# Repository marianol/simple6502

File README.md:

# simple6502

My own take on a simple 6502 single board computer, inspired on Garth Wilson's excellent 6502 Primer, Daryl Rictor, Ben Eater, and my own beautiful C=64 and all the classic 8-bit computers of the late 70s early 80s.

This project exists because of scope creep on my YAsixfive02 project, which is in its 10000 iteration. Which I don't think will ever end.

## Organization

The project is organized as follows:

- /hardware
    - /simple6502 The SBC computer motherboard a.k.a The Project
    - /IO_Card A 6522 IO card with 2 VIAs
    - /protoCard A protoboard card for the simple6502 to build your projects
    - /6502motherboard An untested but complete card connector backplane motherboard. I decided to abandon this in favor of the SBC, i may pick it up later
    - /schematics PDF schematics and renders
    - /gallery images of the completed PCBs
    - /3dmodels Kicad 3D models
- /firmware
    - BIOS and ROM for the simple6502, check the ReadMe
- /docs
    - docs will be here for now only datasheets 

## Design

The goal is to build a simple 6502 SBC with RAM, ROM, IO decoding and a serial interface. An expansion  bus will carry all the address, data and supporting lines to allow adding IO and other hardware expansions. The PCB will be kept at 100x100mm to reduce cost.

For the serial interface I settled on the Motorola 68B50 ACIA, just because I had one lying around. This forced using a 1.8432MHz clock that drives both the CPU and the ACIA. I added a header for an FTDI card to convert the TTL serial to USB. The ACIA is connected to the IO_8 line locating it at 0x7F70 in the memory map.
The jumper J2 next to the header allows you to run the board with the USB 5v rail from the FTDI. IMPORTANT!! This overrides the power switch SW2 and there is no protection built into the board so you should not connect this jumper at the same time as the 5V barrel J7 or the AUX Power header J8.
The bus Slot connectors have pin 27 tied to IO_1 and IO_2 respectively allowing to design expansion cards that can be mapped into memory based on where they are plugged. You still have access to IO_3 to IO_7 in case you want to use those. The Expansion Port J1 is intended to be used with a 40 pin ribbon for ease of development of prototype boards.

I made the PCBs for Revision 1.6 on PCBWay. 

## Status

**Revision 1.6:**

- PCB built and tested.
- BIOS 0.0.1 working on Rev 1.6. Minimal BIOS routines to control the ACIA

## Memory Map

Momory Decocing is done using gates for RAM, ROM and IO. IO_CS line is sent to a 3-8 decoder to get 8 individual IO select lines.
IO line  $\overline{IO\textunderscore08}$ is used for the onboard ACIA for serial communication.
IO lines  $\overline{IO\textunderscore01}$ and $\overline{IO\textunderscore02}$ are sent to pin 27 of Slot 1 and 2 respectively. This allows cards that use this pin to get mapped to the memory based on the Slot they are inserted.

I should have mapped some IO on Zero Page for ease of programming and fast IO, but that is left for another revision, since is too convoluted with gates and better suited for a PAL/GAL. 

### Address Space

- 0x0000 - 0x7EFF : RAM 32K - 256 bytes (31.75k)
- 0x7F00 - 0x7F0F : IO_1 > SLOT 1
- 0x7F10 - 0x7F1F : IO_2 > SLOT 2
- 0x7F20 - 0x7F2F : IO_3
- 0x7F30 - 0x7F3F : IO_4
- 0x7F40 - 0x7F4F : IO_5
- 0x7F50 - 0x7F5F : IO_6
- 0x7F60 - 0x7F6F : IO_7
- 0x7F70 - 0x7F7F : IO_8 > ACIA
- 0x7F80 - 0x7FFF : Not Decoded
- 0x8000 - 0xFFFF : ROM (32K)

## Card Connector Design

The card connector is based on the EDAC 395 series. I decided on the 395-50-520-201 which I had from a previous Apple ][ repair.
Exposed in the connector are:

- Address lines A0..A15
- Data lines D0..D7
- Clock $\phi$ 2
- $\overline{IO{\textunderscore}CS}$, $\overline{RAM{\textunderscore}CS}$ , and $\overline{ROM{\textunderscore}CS}$ chip select lines
- $\overline{RD}$ and $\overline{WR}$ 
- $\overline{RESET}$
- Pin 27 is the slot IO select line. For Slot 1 is $\overline{IO\textunderscore01}$ mapping it to 0x7F00, and for Slot 2 is $\overline{IO\textunderscore02}$ mapping it to 0x7F10.
- IO chip select lines $\overline{IO\textunderscore03}$ .. $\overline{IO\textunderscore07}$.
- $\overline{IRQ}$ and $\overline{NMI}$
- VCC and GND, this are set so if you insert a card backwards you will not short them.
- Pins 21, 24, 33, and 34 are only connected between the 2 slots and have no connection to the mainboard 

## Licence

Licenced under CERN Open Hardware licence CERN-OHL-S v2, see CERN-OHL-S-v2.txt

(c) 2023-2024 Mariano Luna. All rights reserved

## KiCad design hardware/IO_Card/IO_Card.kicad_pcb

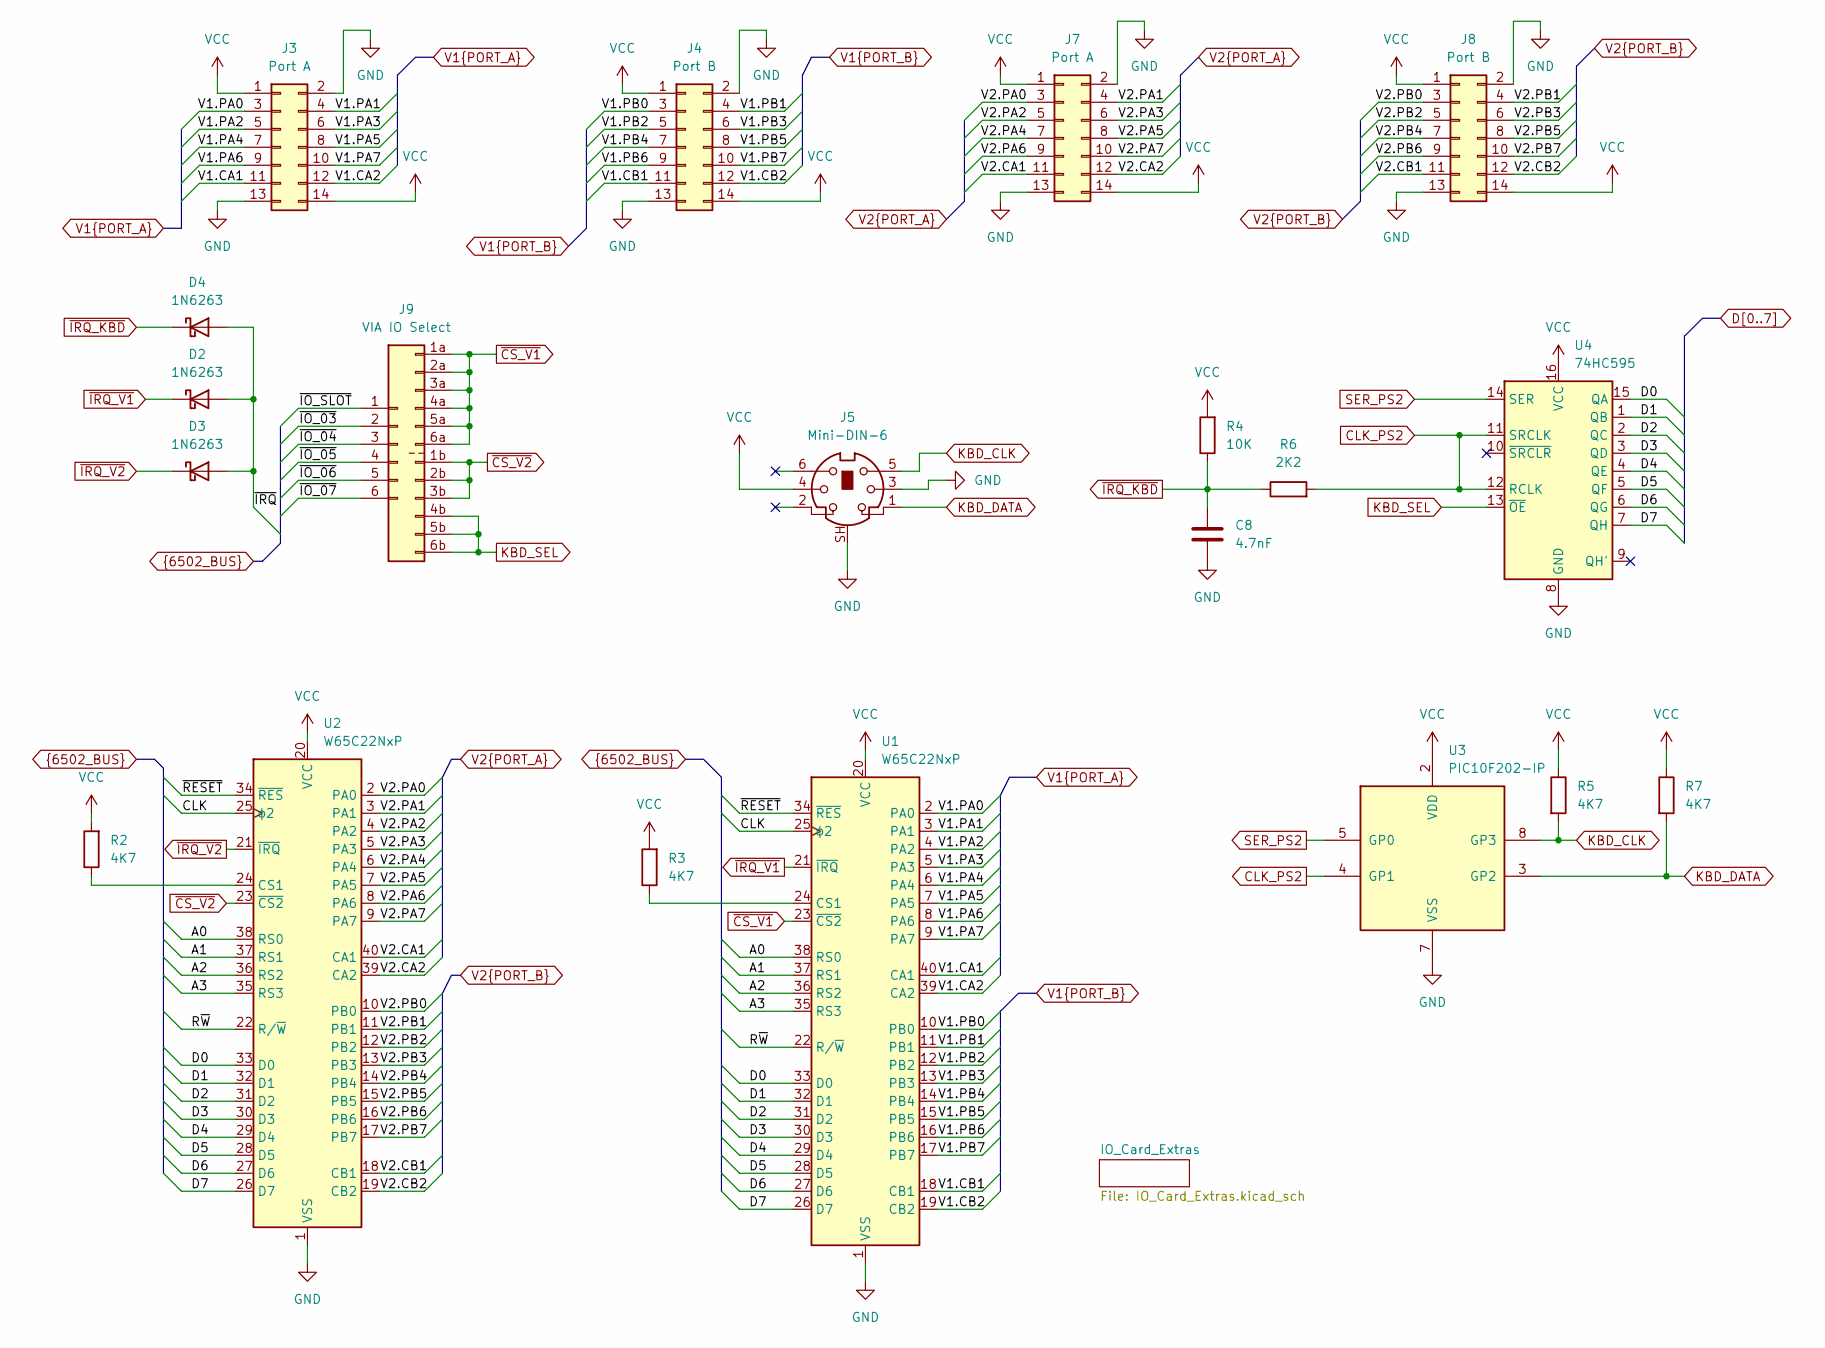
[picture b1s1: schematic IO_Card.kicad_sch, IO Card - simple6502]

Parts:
C8: 4.7nF; C_Disc_D5.0mm_W2.5mm_P5.00mm
D2, D3, D4: 1N6263; D_DO-35_SOD27_P7.62mm_Horizontal
J3, J7: Port A; PinHeader_2x07_P2.54mm_Horizontal
J4, J8: Port B; PinHeader_2x07_P2.54mm_Horizontal
J5: Mini-DIN-6; J_Mini-DIN-6-Shield
J9: VIA IO Select; PinHeader_3x06_P2.54mm_A_B_Vertical
R2, R3: 4K7; R_Axial_DIN0207_L6.3mm_D2.5mm_P10.16mm_Horizontal
R4: 10K; R_Axial_DIN0207_L6.3mm_D2.5mm_P7.62mm_Horizontal
R5, R7: 4K7; R_Axial_DIN0207_L6.3mm_D2.5mm_P7.62mm_Horizontal
R6: 2K2; R_Axial_DIN0207_L6.3mm_D2.5mm_P7.62mm_Horizontal
U1, U2: W65C22NxP; DIP-40_W15.24mm
U3: PIC10F202-IP; DIP-8_W7.62mm
U4: 74HC595; DIP-16_W7.62mm

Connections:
A0: U1.38 (RS0), U2.38 (RS0); also elsewhere on the board
A1: U1.37 (RS1), U2.37 (RS1); also elsewhere on the board
A2: U1.36 (RS2), U2.36 (RS2); also elsewhere on the board
A3: U1.35 (RS3), U2.35 (RS3); also elsewhere on the board
CLK: U1.25 (ϕ2), U2.25 (ϕ2); also elsewhere on the board
CLK_PS2: R6.2, U3.4 (GP1), U4.11 (SRCLK), U4.12 (RCLK)
D0: U1.33 (D0), U2.33 (D0), U4.15 (QA); also elsewhere on the board
D1: U1.32 (D1), U2.32 (D1), U4.1 (QB); also elsewhere on the board
D2: U1.31 (D2), U2.31 (D2), U4.2 (QC); also elsewhere on the board
D3: U1.30 (D3), U2.30 (D3), U4.3 (QD); also elsewhere on the board
D4: U1.29 (D4), U2.29 (D4), U4.4 (QE); also elsewhere on the board
D5: U1.28 (D5), U2.28 (D5), U4.5 (QF); also elsewhere on the board
D6: U1.27 (D6), U2.27 (D6), U4.6 (QG); also elsewhere on the board
D7: U1.26 (D7), U2.26 (D7), U4.7 (QH); also elsewhere on the board
GND: C8.2, J3.2, J3.13, J4.2, J4.13, J5.3, J5.SH, J7.2, J7.13, J8.2, J8.13, U1.1 (VSS), U2.1 (VSS), U3.7 (VSS), U4.8 (GND); also elsewhere on the board
KBD_CLK: J5.5, R5.2, U3.8 (GP3)
KBD_DATA: J5.1, R7.2, U3.3 (GP2)
KBD_SEL: J9.4b, J9.5b, J9.6b, U4.13 (~OE)
unnamed: R3.1, U1.24 (CS1)
unnamed: R2.1, U2.24 (CS1)
R~W: U1.22 (R/~W), U2.22 (R/~W); also elsewhere on the board
SER_PS2: U3.5 (GP0), U4.14 (SER)
V1.CA1: J3.11, U1.40 (CA1)
V1.CA2: J3.12, U1.39 (CA2)
V1.CB1: J4.11, U1.18 (CB1)
V1.CB2: J4.12, U1.19 (CB2)
V1.PA0: J3.3, U1.2 (PA0)
V1.PA1: J3.4, U1.3 (PA1)
V1.PA2: J3.5, U1.4 (PA2)
V1.PA3: J3.6, U1.5 (PA3)
V1.PA4: J3.7, U1.6 (PA4)
V1.PA5: J3.8, U1.7 (PA5)
V1.PA6: J3.9, U1.8 (PA6)
V1.PA7: J3.10, U1.9 (PA7)
V1.PB0: J4.3, U1.10 (PB0)
V1.PB1: J4.4, U1.11 (PB1)
V1.PB2: J4.5, U1.12 (PB2)
V1.PB3: J4.6, U1.13 (PB3)
V1.PB4: J4.7, U1.14 (PB4)
V1.PB5: J4.8, U1.15 (PB5)
V1.PB6: J4.9, U1.16 (PB6)
V1.PB7: J4.10, U1.17 (PB7)
V2.CA1: J7.11, U2.40 (CA1)
V2.CA2: J7.12, U2.39 (CA2)
V2.CB1: J8.11, U2.18 (CB1)
V2.CB2: J8.12, U2.19 (CB2)
V2.PA0: J7.3, U2.2 (PA0)
V2.PA1: J7.4, U2.3 (PA1)
V2.PA2: J7.5, U2.4 (PA2)
V2.PA3: J7.6, U2.5 (PA3)
V2.PA4: J7.7, U2.6 (PA4)
V2.PA5: J7.8, U2.7 (PA5)
V2.PA6: J7.9, U2.8 (PA6)
V2.PA7: J7.10, U2.9 (PA7)
V2.PB0: J8.3, U2.10 (PB0)
V2.PB1: J8.4, U2.11 (PB1)
V2.PB2: J8.5, U2.12 (PB2)
V2.PB3: J8.6, U2.13 (PB3)
V2.PB4: J8.7, U2.14 (PB4)
V2.PB5: J8.8, U2.15 (PB5)
V2.PB6: J8.9, U2.16 (PB6)
V2.PB7: J8.10, U2.17 (PB7)
VCC: J3.1, J3.14, J4.1, J4.14, J5.4, J7.1, J7.14, J8.1, J8.14, R2.2, R3.2, R4.2, R5.1, R7.1, U1.20 (VCC), U2.20 (VCC), U3.2 (VDD), U4.16 (VCC); also elsewhere on the board
~CS_V1: J9.1a, J9.2a, J9.3a, J9.4a, J9.5a, J9.6a, U1.23 (~CS2)
~CS_V2: J9.1b, J9.2b, J9.3b, U2.23 (~CS2)
~IO_03: J9.2; also elsewhere on the board
~IO_04: J9.3; also elsewhere on the board
~IO_05: J9.4; also elsewhere on the board
~IO_06: J9.5; also elsewhere on the board
~IO_07: J9.6; also elsewhere on the board
~IO_SLOT: J9.1; also elsewhere on the board
~IRQ_KBD: C8.1, D4.1 (K), R4.1, R6.1
~IRQ_V1: D2.1 (K), U1.21 (~IRQ)
~IRQ_V2: D3.1 (K), U2.21 (~IRQ)
~IRQ: D2.2 (A), D3.2 (A), D4.2 (A); also elsewhere on the board
~RESET: U1.34 (~RES), U2.34 (~RES); also elsewhere on the board

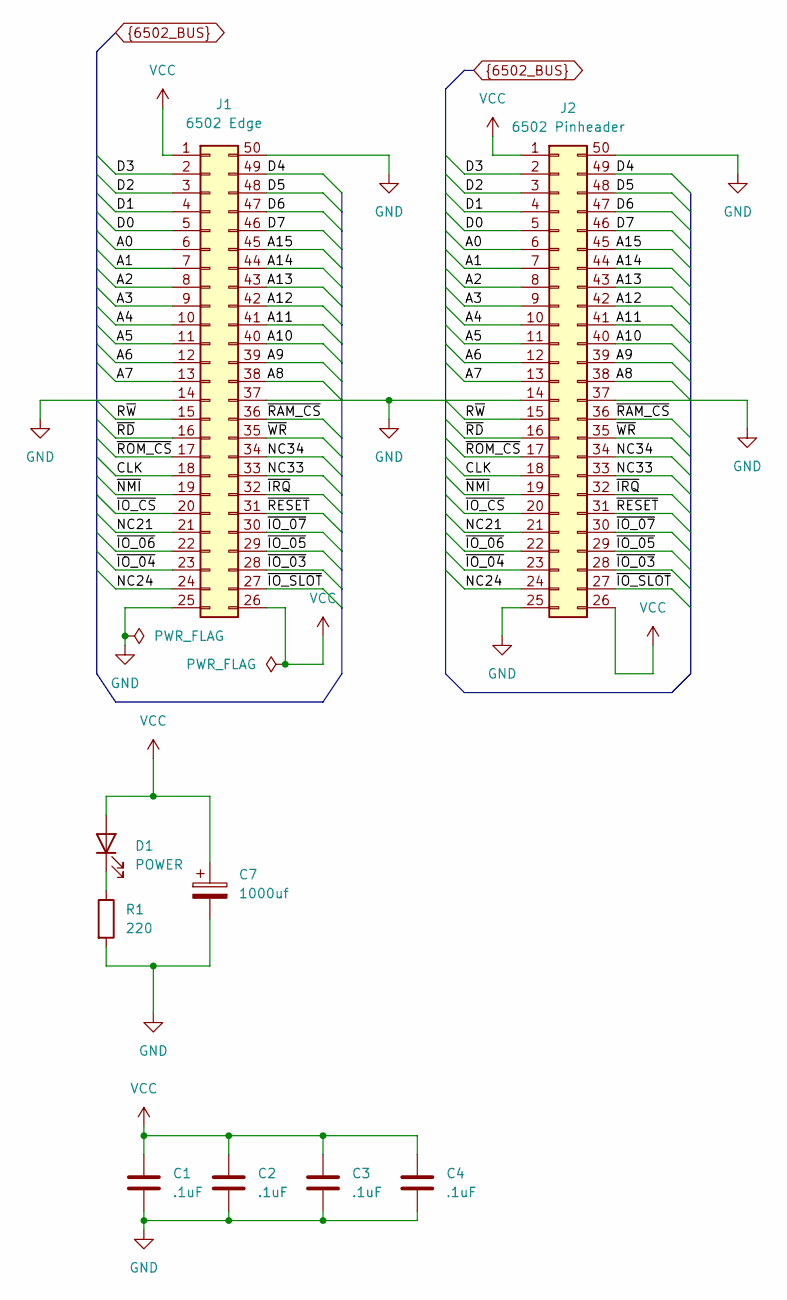
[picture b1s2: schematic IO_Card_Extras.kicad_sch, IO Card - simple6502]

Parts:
C1, C2, C3, C4: .1uF; C_1206_3216Metric_Pad1.33x1.80mm_HandSolder
C7: 1000uf; CP_Radial_D5.0mm_P2.50mm
D1: POWER; LED_D3.0mm
J1: 6502 Edge; BUS_EdgePCB_Apple_2
J2: 6502 Pinheader; PinHeader_2x25_P2.54mm_Vertical_CounterClockWise
R1: 220; R_Axial_DIN0207_L6.3mm_D2.5mm_P10.16mm_Horizontal

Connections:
A0: J1.6, J2.6; also elsewhere on the board
A1: J1.7, J2.7; also elsewhere on the board
A2: J1.8, J2.8; also elsewhere on the board
A3: J1.9, J2.9; also elsewhere on the board
A4: J1.10, J2.10
A5: J1.11, J2.11
A6: J1.12, J2.12
A7: J1.13, J2.13
A8: J1.38, J2.38
A9: J1.39, J2.39
A10: J1.40, J2.40
A11: J1.41, J2.41
A12: J1.42, J2.42
A13: J1.43, J2.43
A14: J1.44, J2.44
A15: J1.45, J2.45
CLK: J1.18, J2.18; also elsewhere on the board
D0: J1.5, J2.5; also elsewhere on the board
D1: J1.4, J2.4; also elsewhere on the board
D2: J1.3, J2.3; also elsewhere on the board
D3: J1.2, J2.2; also elsewhere on the board
D4: J1.49, J2.49; also elsewhere on the board
D5: J1.48, J2.48; also elsewhere on the board
D6: J1.47, J2.47; also elsewhere on the board
D7: J1.46, J2.46; also elsewhere on the board
GND: C1.2, C2.2, C3.2, C4.2, C7.2, J1.14, J1.25, J1.37, J1.50, J2.14, J2.25, J2.37, J2.50, R1.2; also elsewhere on the board
NC21: J1.21, J2.21
NC24: J1.24, J2.24
NC33: J1.33, J2.33
NC34: J1.34, J2.34
unnamed: D1.1 (K), R1.1
R~W: J1.15, J2.15; also elsewhere on the board
VCC: C1.1, C2.1, C3.1, C4.1, C7.1, D1.2 (A), J1.1, J1.26, J2.1, J2.26; also elsewhere on the board
~IO_03: J1.28, J2.28; also elsewhere on the board
~IO_04: J1.23, J2.23; also elsewhere on the board
~IO_05: J1.29, J2.29; also elsewhere on the board
~IO_06: J1.22, J2.22; also elsewhere on the board
~IO_07: J1.30, J2.30; also elsewhere on the board
~IO_CS: J1.20, J2.20
~IO_SLOT: J1.27, J2.27; also elsewhere on the board
~IRQ: J1.32, J2.32; also elsewhere on the board
~NMI: J1.19, J2.19
~RAM_CS: J1.36, J2.36
~RD: J1.16, J2.16
~RESET: J1.31, J2.31; also elsewhere on the board
~ROM_CS: J1.17, J2.17
~WR: J1.35, J2.35

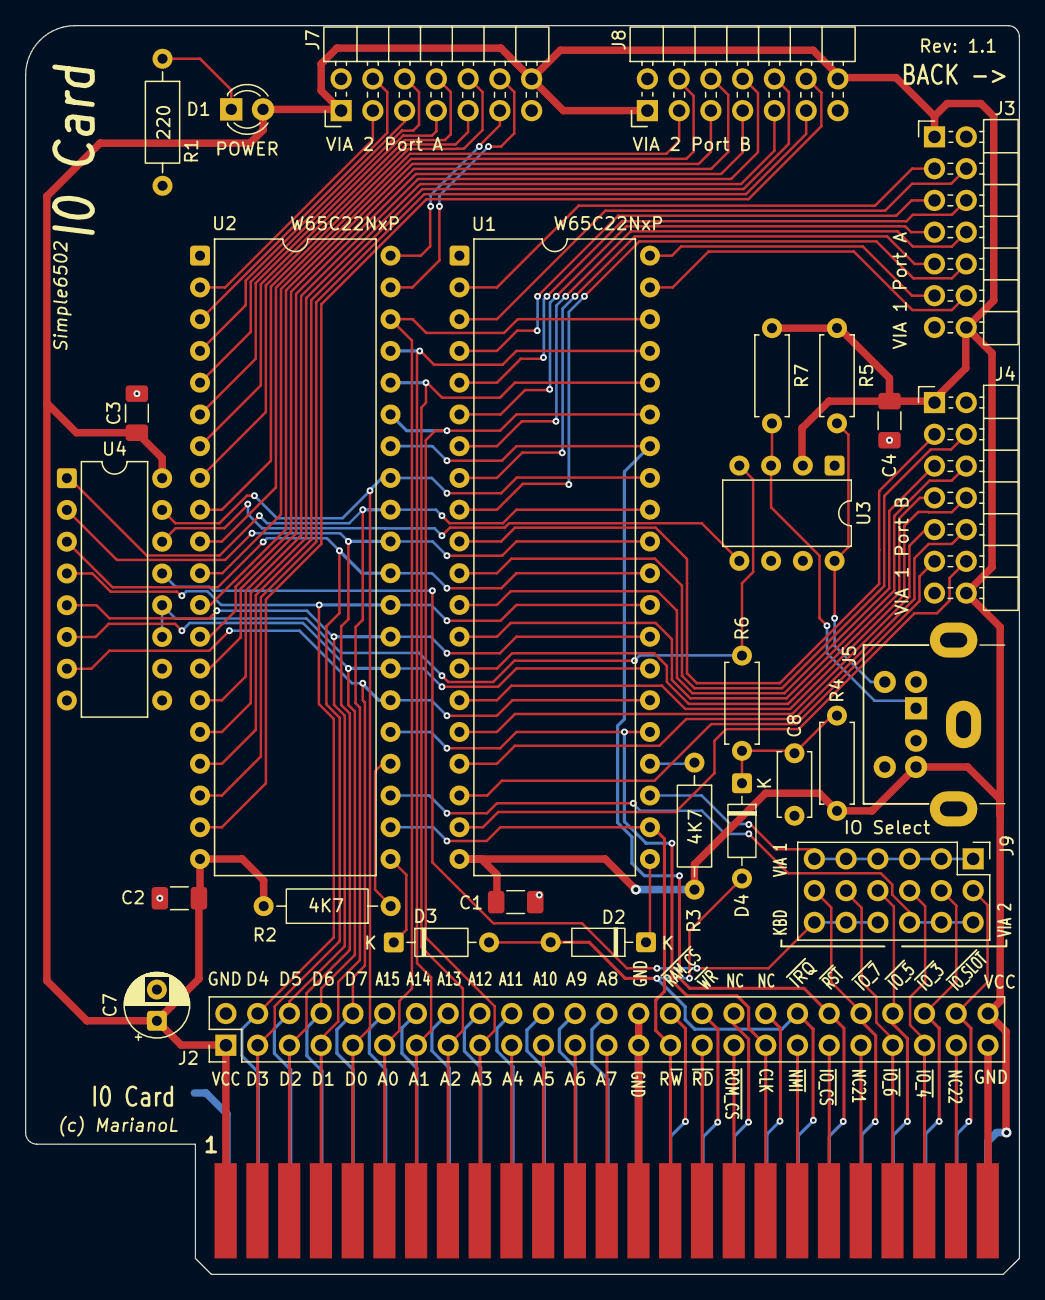
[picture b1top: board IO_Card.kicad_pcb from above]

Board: 2 copper layers, 79.5 x 99.9 mm, 29 parts (0 on the bottom side), 99 nets.

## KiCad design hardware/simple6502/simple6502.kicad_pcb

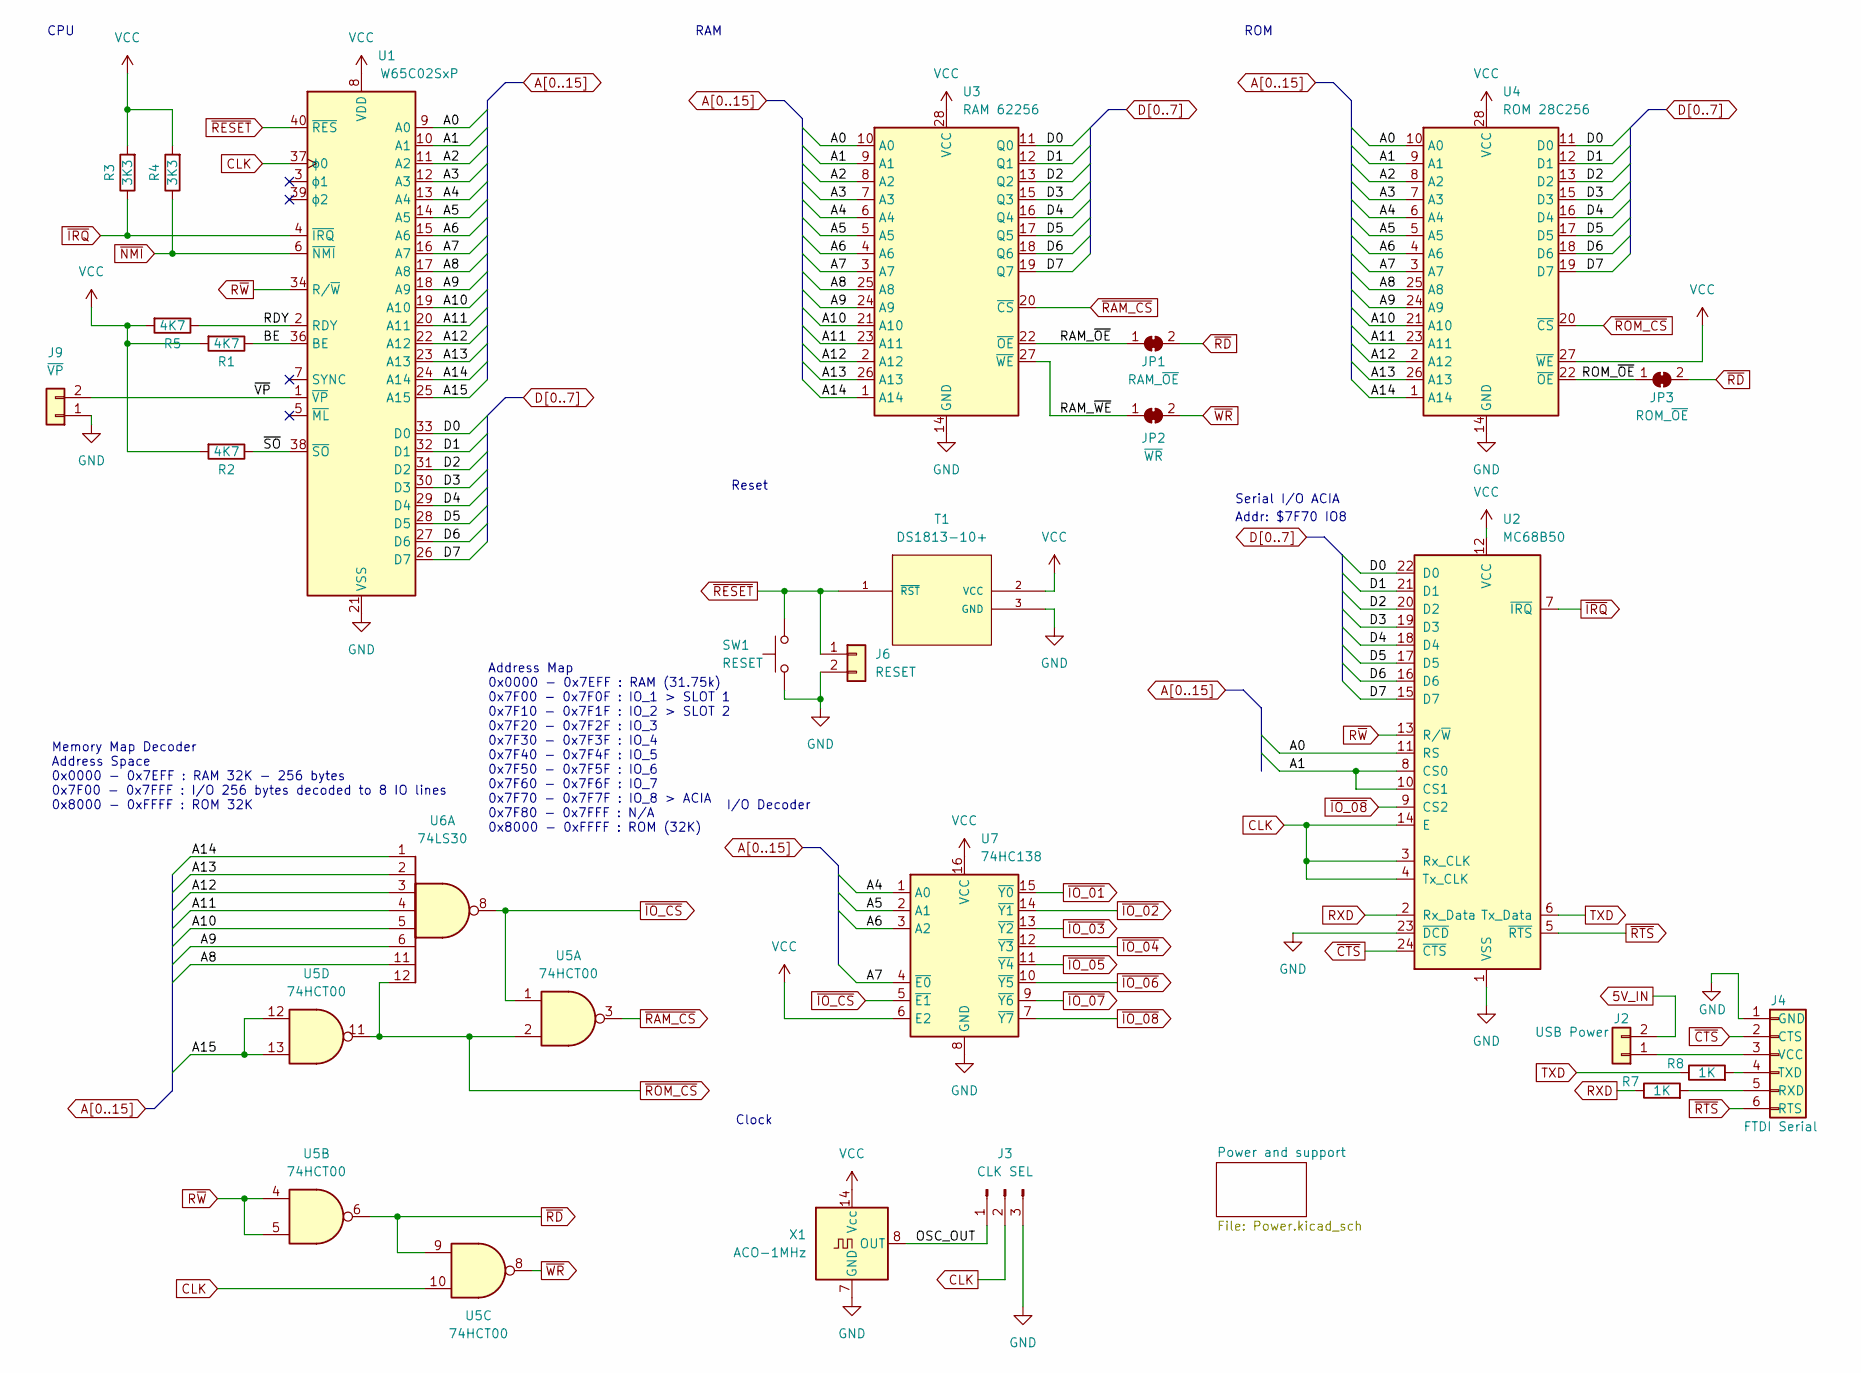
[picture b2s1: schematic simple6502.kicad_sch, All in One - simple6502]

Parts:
J2: USB Power; PinHeader_1x02_P2.54mm_Vertical
J3: CLK SEL; PinHeader_1x03_P2.54mm_Vertical
J4: FTDI Serial; PinSocket_1x06_P2.54mm_Vertical
J6: RESET; PinHeader_1x02_P2.54mm_Vertical
J9: ~{VP}; SolderJumper-2_P1.3mm_Open_RoundedPad1.0x1.5mm
JP1: RAM_~{OE}; SolderJumper-2_P1.3mm_Bridged_RoundedPad1.0x1.5mm
JP2: ~{WR}; SolderJumper-2_P1.3mm_Bridged_RoundedPad1.0x1.5mm
JP3: ROM_~{OE}; SolderJumper-2_P1.3mm_Bridged_RoundedPad1.0x1.5mm
R1, R2, R5: 4K7; R_Axial_DIN0204_L3.6mm_D1.6mm_P7.62mm_Horizontal
R3, R4: 3K3; R_Axial_DIN0204_L3.6mm_D1.6mm_P7.62mm_Horizontal
R7, R8: 1K; R_Axial_DIN0204_L3.6mm_D1.6mm_P7.62mm_Horizontal
SW1: RESET; SW_TH_Tactile_Omron_B3F-10xx
T1: DS1813-10+; 21-0248A
U1: W65C02SxP; DIP-40_W15.24mm_Socket
U2: MC68B50; DIP-24_W15.24mm_Socket
U3: RAM 62256; DIP-28_W15.24mm_Socket
U4: ROM 28C256; DIP-28_W15.24mm_Socket
U5: 74HCT00; DIP-14_W7.62mm_Socket
U6: 74LS30; DIP-14_W7.62mm_Socket
U7: 74HC138; DIP-16_W7.62mm_Socket
X1: ACO-1MHz; Oscillator_DIP-14

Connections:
5V_IN: J2.2; also elsewhere on the board
/BE: R1.1, U1.36 (BE)
/OSC_OUT: J3.1, X1.8 (OUT)
/RAM_~OE: JP1.1 (A), U3.22 (~OE)
/RAM_~WE: JP2.1 (A), U3.27 (~WE)
/RDY: R5.1, U1.2 (RDY)
/ROM_~OE: JP3.1 (A), U4.22 (~OE)
/~SO: R2.1, U1.38 (~SO)
/~VP: J9.2, U1.1 (~VP)
A0: U1.9 (A0), U2.11 (RS), U3.10 (A0), U4.10 (A0); also elsewhere on the board
A1: U1.10 (A1), U2.8 (CS0), U2.10 (CS1), U3.9 (A1), U4.9 (A1); also elsewhere on the board
A2: U1.11 (A2), U3.8 (A2), U4.8 (A2); also elsewhere on the board
A3: U1.12 (A3), U3.7 (A3), U4.7 (A3); also elsewhere on the board
A4: U1.13 (A4), U3.6 (A4), U4.6 (A4), U7.1 (A0); also elsewhere on the board
A5: U1.14 (A5), U3.5 (A5), U4.5 (A5), U7.2 (A1); also elsewhere on the board
A6: U1.15 (A6), U3.4 (A6), U4.4 (A6), U7.3 (A2); also elsewhere on the board
A7: U1.16 (A7), U3.3 (A7), U4.3 (A7), U7.4 (~E0); also elsewhere on the board
A8: U1.17 (A8), U3.25 (A8), U4.25 (A8), U6.11; also elsewhere on the board
A9: U1.18 (A9), U3.24 (A9), U4.24 (A9), U6.6; also elsewhere on the board
A10: U1.19 (A10), U3.21 (A10), U4.21 (A10), U6.5; also elsewhere on the board
A11: U1.20 (A11), U3.23 (A11), U4.23 (A11), U6.4; also elsewhere on the board
A12: U1.22 (A12), U3.2 (A12), U4.2 (A12), U6.3; also elsewhere on the board
A13: U1.23 (A13), U3.26 (A13), U4.26 (A13), U6.2; also elsewhere on the board
A14: U1.24 (A14), U3.1 (A14), U4.1 (A14), U6.1; also elsewhere on the board
A15: U1.25 (A15), U5.12, U5.13; also elsewhere on the board
CLK: J3.2, U1.37 (ϕ0), U2.3 (Rx_CLK), U2.4 (Tx_CLK), U2.14 (E), U5.10; also elsewhere on the board
D0: U1.33 (D0), U2.22 (D0), U3.11 (Q0), U4.11 (D0); also elsewhere on the board
D1: U1.32 (D1), U2.21 (D1), U3.12 (Q1), U4.12 (D1); also elsewhere on the board
D2: U1.31 (D2), U2.20 (D2), U3.13 (Q2), U4.13 (D2); also elsewhere on the board
D3: U1.30 (D3), U2.19 (D3), U3.15 (Q3), U4.15 (D3); also elsewhere on the board
D4: U1.29 (D4), U2.18 (D4), U3.16 (Q4), U4.16 (D4); also elsewhere on the board
D5: U1.28 (D5), U2.17 (D5), U3.17 (Q5), U4.17 (D5); also elsewhere on the board
D6: U1.27 (D6), U2.16 (D6), U3.18 (Q6), U4.18 (D6); also elsewhere on the board
D7: U1.26 (D7), U2.15 (D7), U3.19 (Q7), U4.19 (D7); also elsewhere on the board
GND: J3.3, J4.1 (GND), J6.2, J9.1, SW1.1, T1.3 (GND), U1.21 (VSS), U2.1 (VSS), U2.23 (~DCD), U3.14 (GND), U4.14 (GND), U7.8 (GND), X1.7 (GND); also elsewhere on the board
unnamed: J2.1, J4.3 (VCC)
unnamed: J4.5 (RXD), R7.2
unnamed: J4.4 (TXD), R8.2
RXD: R7.1, U2.2 (Rx_Data)
R~W: U1.34 (R/~W), U2.13 (R/~W), U5.4, U5.5; also elsewhere on the board
TXD: R8.1, U2.6 (Tx_Data)
VCC: R1.2, R2.2, R3.2, R4.2, R5.2, T1.2 (VCC), U1.8 (VDD), U2.12 (VCC), U3.28 (VCC), U4.27 (~WE), U4.28 (VCC), U7.6 (E2), U7.16 (VCC), X1.14 (Vcc); also elsewhere on the board
~CTS: J4.2 (CTS), U2.24 (~CTS)
~IO_02: U7.14 (~Y1); also elsewhere on the board
~IO_03: U7.13 (~Y2); also elsewhere on the board
~IO_04: U7.12 (~Y3); also elsewhere on the board
~IO_05: U7.11 (~Y4); also elsewhere on the board
~IO_06: U7.10 (~Y5); also elsewhere on the board
~IO_07: U7.9 (~Y6); also elsewhere on the board
~IO_08: U2.9 (CS2), U7.7 (~Y7)
~IO_CS: U5.1, U6.8, U7.5 (~E1); also elsewhere on the board
~IRQ: R3.1, U1.4 (~IRQ), U2.7 (~IRQ); also elsewhere on the board
~NMI: R4.1, U1.6 (~NMI); also elsewhere on the board
~RAM_CS: U3.20 (~CS), U5.3; also elsewhere on the board
~RD: JP1.2 (B), JP3.2 (B), U5.6, U5.9; also elsewhere on the board
~RESET: J6.1, SW1.2, T1.1 (~RST), U1.40 (~RES); also elsewhere on the board
~ROM_CS: U4.20 (~CS), U5.2, U5.11, U6.12; also elsewhere on the board
~RTS: J4.6 (RTS), U2.5 (~RTS)
~WR: JP2.2 (B), U5.8; also elsewhere on the board

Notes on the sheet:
Addr: $7F70 IO8
Reset
Clock
Memory Map Decoder Address Space 0x0000 - 0x7EFF : RAM 32K - 256 bytes 0x7F00 - 0x7FFF : I/O 256 bytes decoded to 8 IO lines 0x8000 - 0xFFFF : ROM 32K
Serial I/O ACIA
RAM
CPU
ROM
Address Map 0x0000 - 0x7EFF : RAM (31.75k) 0x7F00 - 0x7F0F : IO_1 > SLOT 1 0x7F10 - 0x7F1F : IO_2 > SLOT 2 0x7F20 - 0x7F2F : IO_3 0x7F30 - 0x7F3F : IO_4 0x7F40 - 0x7F4F : IO_5 0x7F50 - 0x7F5F : IO_6 0x7F60 - 0x7F6F : IO_7 0x7F70 - 0x7F7F : IO_8 > ACIA 0x7F80 - 0x7FFF : N/A 0x8000 - 0xFFFF : ROM (32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
I/O Decoder

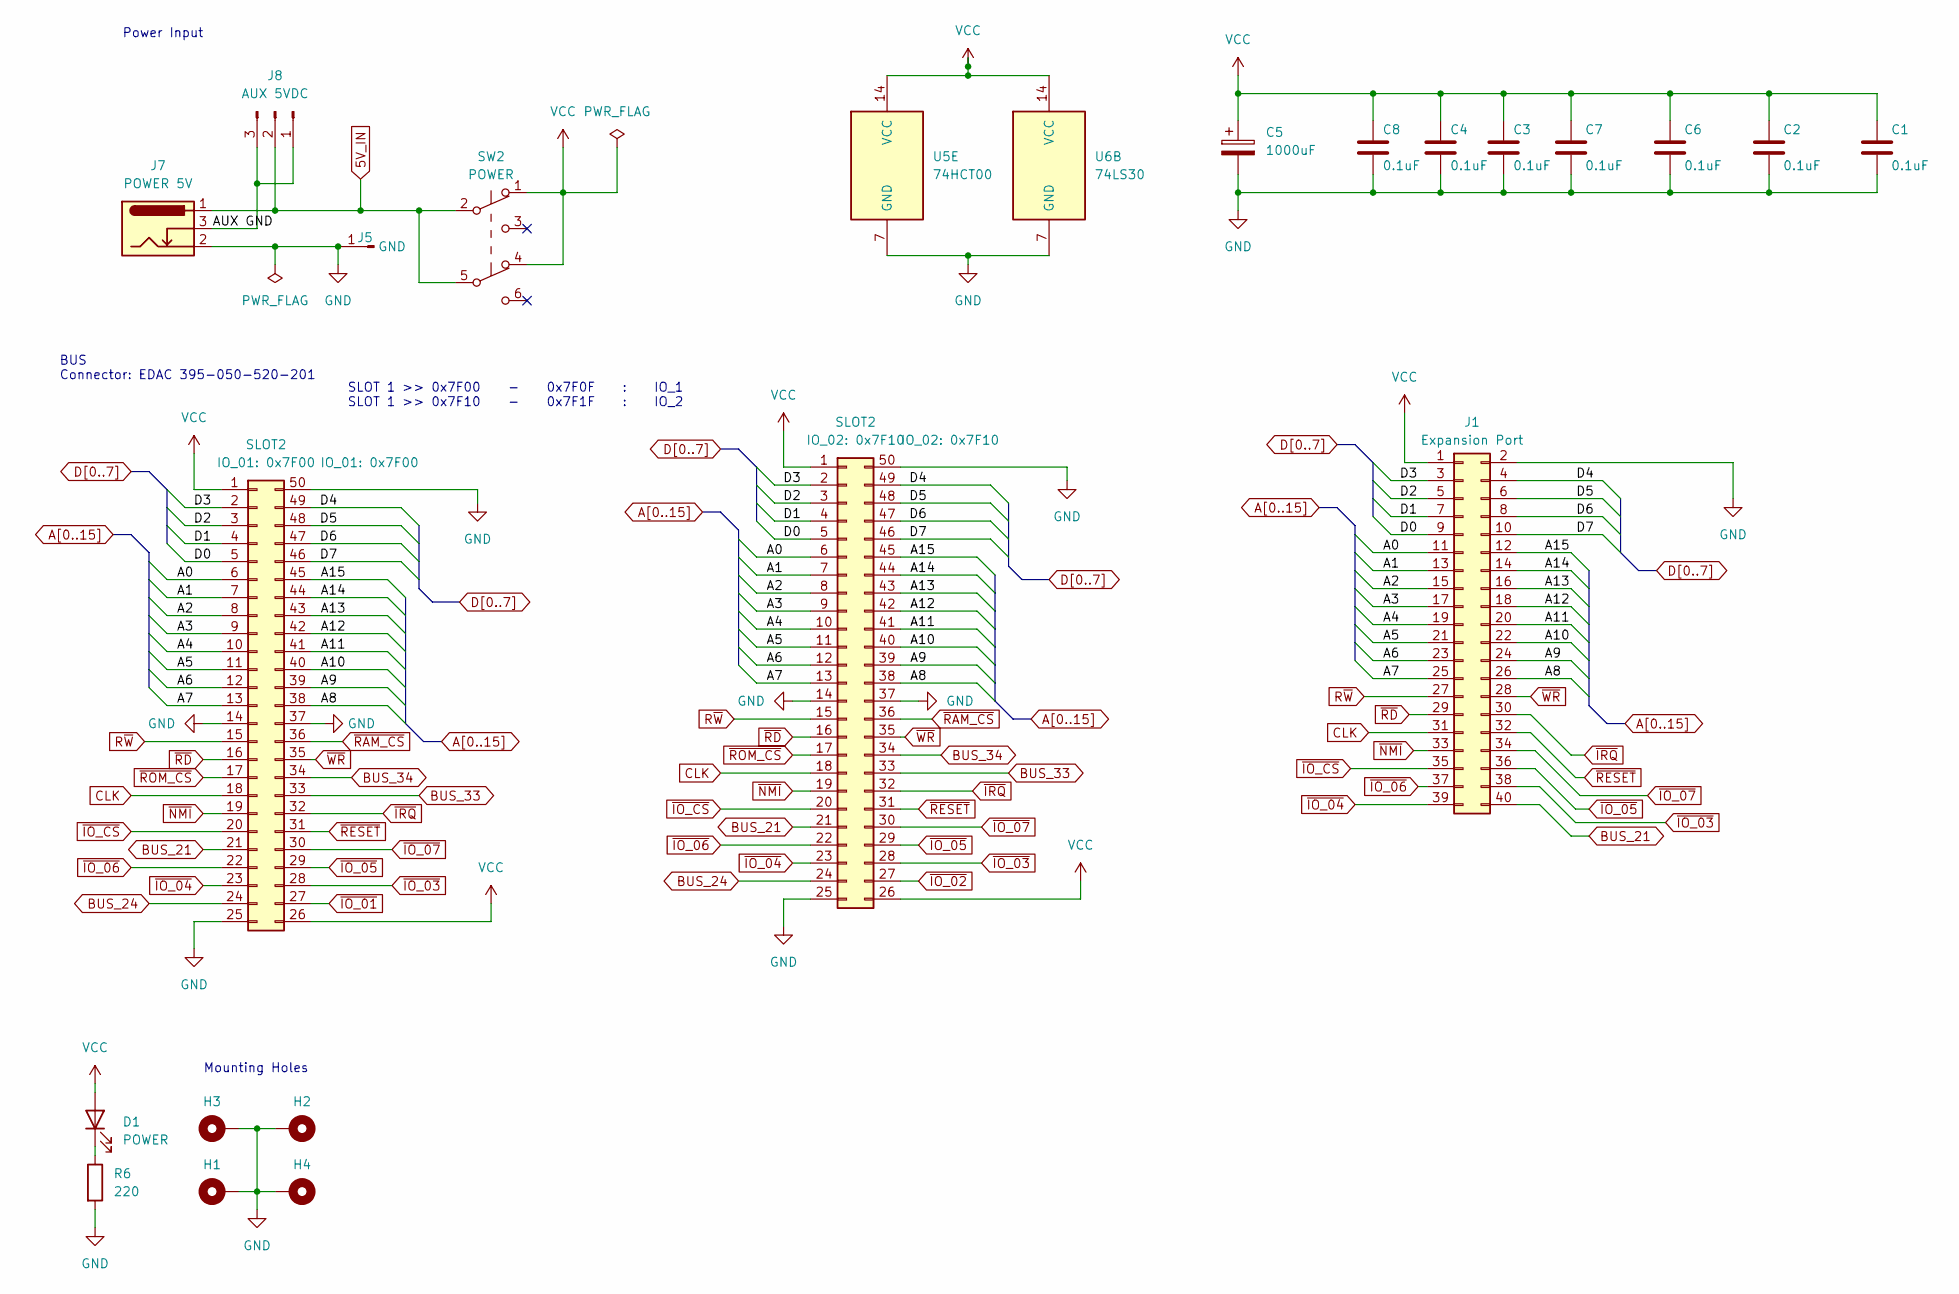
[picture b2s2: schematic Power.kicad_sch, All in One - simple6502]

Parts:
C1, C2, C3, C4, C6, C7, C8: 0.1uF; C_Disc_D3.0mm_W1.6mm_P2.50mm
C5: 1000uF; CP_Radial_D6.3mm_P2.50mm
D1: POWER; LED_D3.0mm
H1, H2, H3, H4: M; MountingHole_2.7mm_M2.5_Pad_Via
J1: Expansion Port; PinHeader_2x20_P2.54mm_Vertical
J5: GND; PinHeader_1x01_P2.54mm_Vertical
J7: POWER 5V; BarrelJack_Horizontal
J8: AUX 5VDC; PinHeader_1x03_P2.54mm_Vertical
R6: 220; R_Axial_DIN0204_L3.6mm_D1.6mm_P7.62mm_Horizontal
SLOT2: IO_02: 0x7F10; EDAC 395-050-520-201
SW2: POWER; SW_Push_2P2T_Toggle_CK_PVA2OAH5xxxxxxV2
U5: 74HCT00; DIP-14_W7.62mm_Socket
U6: 74LS30; DIP-14_W7.62mm_Socket

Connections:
5V_IN: J7.1, J8.2, SW2.2 (B), SW2.5 (B); also elsewhere on the board
/Power and support/AUX GND: J7.3, J8.1, J8.3
A0: J1.11, SLOT2.6; also elsewhere on the board
A1: J1.13, SLOT2.7; also elsewhere on the board
A2: J1.15, SLOT2.8; also elsewhere on the board
A3: J1.17, SLOT2.9; also elsewhere on the board
A4: J1.19, SLOT2.10; also elsewhere on the board
A5: J1.21, SLOT2.11; also elsewhere on the board
A6: J1.23, SLOT2.12; also elsewhere on the board
A7: J1.25, SLOT2.13; also elsewhere on the board
A8: J1.26, SLOT2.38; also elsewhere on the board
A9: J1.24, SLOT2.39; also elsewhere on the board
A10: J1.22, SLOT2.40; also elsewhere on the board
A11: J1.20, SLOT2.41; also elsewhere on the board
A12: J1.18, SLOT2.42; also elsewhere on the board
A13: J1.16, SLOT2.43; also elsewhere on the board
A14: J1.14, SLOT2.44; also elsewhere on the board
A15: J1.12, SLOT2.45; also elsewhere on the board
BUS_21: J1.40, SLOT2.21; also elsewhere on the board
BUS_24: SLOT2.24; also elsewhere on the board
BUS_33: SLOT2.33; also elsewhere on the board
BUS_34: SLOT2.34; also elsewhere on the board
CLK: J1.31, SLOT2.18; also elsewhere on the board
D0: J1.9, SLOT2.5; also elsewhere on the board
D1: J1.7, SLOT2.4; also elsewhere on the board
D2: J1.5, SLOT2.3; also elsewhere on the board
D3: J1.3, SLOT2.2; also elsewhere on the board
D4: J1.4, SLOT2.49; also elsewhere on the board
D5: J1.6, SLOT2.48; also elsewhere on the board
D6: J1.8, SLOT2.47; also elsewhere on the board
D7: J1.10, SLOT2.46; also elsewhere on the board
GND: C1.2, C2.2, C3.2, C4.2, C5.2, C6.2, C7.2, C8.2, H1.1, H2.1, H3.1, H4.1, J1.2, J5.1, J7.2, R6.2, SLOT2.14, SLOT2.25, SLOT2.37, SLOT2.50, U5.7 (GND), U6.7 (GND); also elsewhere on the board
unnamed: D1.1 (K), R6.1
R~W: J1.27, SLOT2.15; also elsewhere on the board
VCC: C1.1, C2.1, C3.1, C4.1, C5.1, C6.1, C7.1, C8.1, D1.2 (A), J1.1, SLOT2.1, SLOT2.26, SW2.1 (A), SW2.4 (A), U5.14 (VCC), U6.14 (VCC); also elsewhere on the board
~IO_03: J1.38, SLOT2.28; also elsewhere on the board
~IO_04: J1.39, SLOT2.23; also elsewhere on the board
~IO_05: J1.36, SLOT2.29; also elsewhere on the board
~IO_06: J1.37, SLOT2.22; also elsewhere on the board
~IO_07: J1.34, SLOT2.30; also elsewhere on the board
~IO_CS: J1.35, SLOT2.20; also elsewhere on the board
~IRQ: J1.30, SLOT2.32; also elsewhere on the board
~NMI: J1.33, SLOT2.19; also elsewhere on the board
~RAM_CS: SLOT2.36; also elsewhere on the board
~RD: J1.29, SLOT2.16; also elsewhere on the board
~RESET: J1.32, SLOT2.31; also elsewhere on the board
~ROM_CS: SLOT2.17; also elsewhere on the board
~WR: J1.28, SLOT2.35; also elsewhere on the board

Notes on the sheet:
Power Input
SLOT 1 >> 0x7F00 - 0x7F0F : IO_1 SLOT 1 >> 0x7F10 - 0x7F1F : IO_2
BUS Connector: EDAC 395-050-520-201
Mounting Holes

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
